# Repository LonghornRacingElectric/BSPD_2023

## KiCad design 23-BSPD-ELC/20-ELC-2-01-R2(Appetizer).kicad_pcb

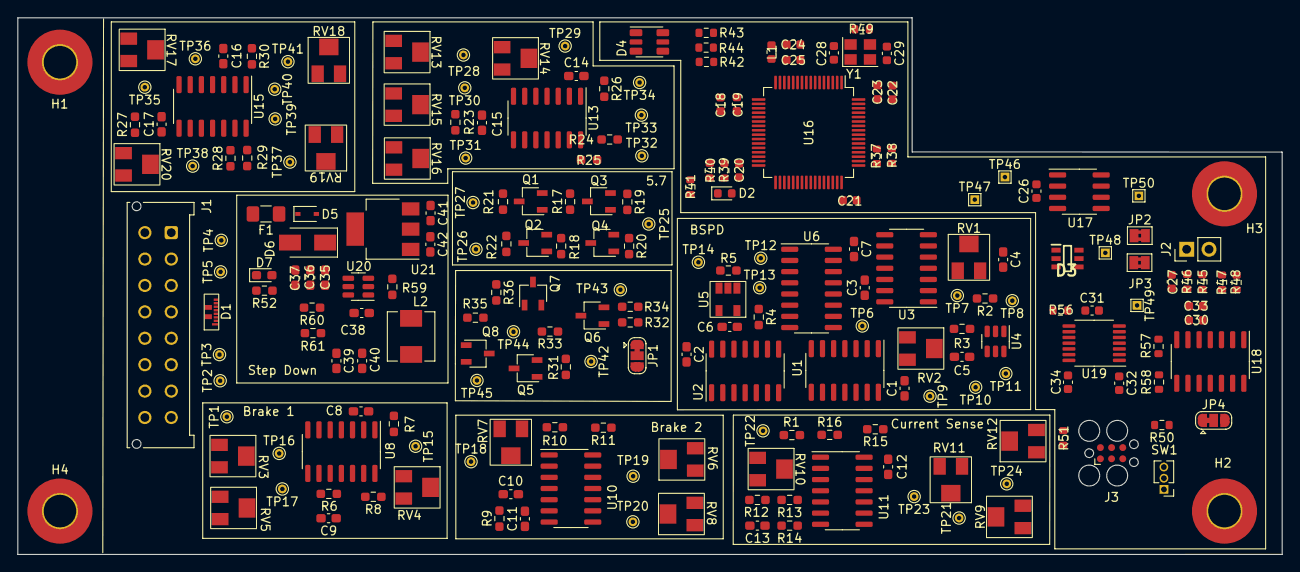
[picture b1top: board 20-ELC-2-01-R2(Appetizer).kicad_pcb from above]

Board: 2 copper layers, 143.6 x 61.0 mm, 218 parts (0 on the bottom side), 109 nets, no tracks yet.

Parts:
C1, C2, C3, C6, C7, C8, C9, C10, C11, C12, C13, C14, C15, C16, C17: 0.1uF; C_0603_1608Metric_Pad1.08x0.95mm_HandSolder
C4, C5, C39, C40, C42: 22uF; C_0603_1608Metric_Pad1.08x0.95mm_HandSolder
C18: 4u7; C_0603_1608Metric
C19, C20, C21, C22, C23: 100n; C_0603_1608Metric
C24: 1u; C_0603_1608Metric
C25: 10n; C_0603_1608Metric
C26: 0u1; C_0603_1608Metric
C27: 4.7n; C_0603_1608Metric
C28, C29: 10p; C_0603_1608Metric
C30, C32, C34: .1uF; C_0603_1608Metric
C31: 1uF; C_0603_1608Metric
C33: 10uF; C_0603_1608Metric
C35, C36: 10uF; C_0603_1608Metric_Pad1.08x0.95mm_HandSolder
C37, C38: 100nF; C_0603_1608Metric_Pad1.08x0.95mm_HandSolder
C41: 1uF; C_0603_1608Metric_Pad1.08x0.95mm_HandSolder
D1: ESD7016MUTAG
D2: RED; LED_0603_1608Metric
D3: DT1446-04TS-7; SOT95P280X100-6N
D4: SMLVN6RGB; LED_ROHM_SMLVN6
D5: 32V; D_SOD-323
D6: 0.7dV; D_SMA
D7: LED; LED_0603_1608Metric_Pad1.05x0.95mm_HandSolder
F1: 2A; Fuse_1206_3216Metric_Pad1.42x1.75mm_HandSolder
H1, H2, H3, H4: MountingHole; MountingHole_3.7mm_Pad_TopBottom
J1: Conn_02x08_Counter_Clockwise; Molex_Micro-Fit_3.0_43045-1612_2x08_P3.00mm_Vertical
J2: Conn_01x02; PinHeader_1x02_P2.54mm_Vertical
J3: SWD; Tag-Connect_TC2030-IDC-FP_2x03_P1.27mm_Vertical
JP1, JP4: Jumper_3_Bridged12; SolderJumper-3_P1.3mm_Bridged12_RoundedPad1.0x1.5mm
JP2, JP3: SolderJumper-2_P1.3mm_Bridged2Bar_Pad1.0x1.5mm
L1: 68n; L_0603_1608Metric
L2: 4u7; L_Sunlord_MWSA0518_5.4x5.2mm
Q1, Q2: Q_PMOS_GSD; TSOT-23
Q3, Q4, Q5, Q6: Q_NMOS_GSD-Device; TSOT-23
Q7, Q8: Q_PMOS_DSG; TSOT-23
R1, R2, R3, R4, R7, R8, R10, R11, R15, R16, R17, R19, R20, R21, R22, R24, R25, R26, R28, R29, R30, R33, R34, R35, R36: 10k; R_0603_1608Metric_Pad0.98x0.95mm_HandSolder
R5: 100k; R_0603_1608Metric_Pad0.98x0.95mm_HandSolder
R6, R9, R12: 510k; R_0603_1608Metric_Pad0.98x0.95mm_HandSolder
R13, R14: 150; R_0603_1608Metric_Pad0.98x0.95mm_HandSolder
R18: 250; R_0603_1608Metric_Pad0.98x0.95mm_HandSolder
R23, R27: 510; R_0603_1608Metric_Pad0.98x0.95mm_HandSolder
R31, R32: 25; R_0603_1608Metric_Pad0.98x0.95mm_HandSolder
R37, R38, R39, R40: 2k2; R_0603_1608Metric
R41: 100; R_0603_1608Metric
R42, R43, R44: 220; R_0603_1608Metric
R45, R46, R47, R48: 120; R_0603_1608Metric
R49: 47; R_0603_1608Metric
R50: 10K; R_0603_1608Metric
R51: 22; R_0603_1608Metric
R52: 470R; R_0603_1608Metric_Pad0.98x0.95mm_HandSolder
R56: 100k; R_0603_1608Metric
R57, R58: 10k; R_0603_1608Metric
R59, R60: 10K; R_0603_1608Metric_Pad0.98x0.95mm_HandSolder
R61: 54.9K; R_0603_1608Metric_Pad0.98x0.95mm_HandSolder
RV1, RV2, RV3, RV4, RV5, RV6, RV7, RV8, RV9, RV10, RV11, RV12: PVG5A104C03R00; PVG5A
RV13, RV14, RV17, RV18: 10k; PVG5A
RV15, RV16, RV19, RV20: R_POT_TRIM-Device; PVG5A
SW1: SW_SPDT; PinHeader_1x03_P1.27mm_Vertical
TP1, TP2, TP3, TP4, TP5, TP26, TP27, TP42, TP43, TP44, TP45: TestPoint-Connector; TestPoint_THTPad_D1.0mm_Drill0.5mm
TP6, TP7, TP8, TP9, TP10, TP11, TP12, TP13, TP14, TP15, TP16, TP17, TP18, TP19, TP20, TP21, TP22, TP23, TP24, TP25, TP28, TP29, TP30, TP31, TP32, TP33, TP34, TP35, TP36, TP37, TP38, TP39, TP40, TP41: TestPoint; TestPoint_THTPad_D1.0mm_Drill0.5mm
TP46, TP47, TP48, TP49, TP50: TestPoint_THTPad_1.0x1.0mm_Drill0.5mm
U1: SN74ALS32DR; SOIC-14_3.9x8.7mm_P1.27mm
U2: 74HC04D,653; SO-14_3.9x8.65mm_P1.27mm
U3: 74HC08D,653; SOIC-14_3.9x8.7mm_P1.27mm
U4: 74LVC2G17DBVE4; SOT-23-6
U5: APX823-44W5G-7; AXP823-44W5G-7
U6: CD4043BDR; SOIC-16_3.9x9.9mm_P1.27mm
U8, U10, U11, U13, U15: LM239; SO-14_3.9x8.65mm_P1.27mm
U16: STM32F105RCTx; LQFP-64_10x10mm_P0.5mm
U17: SN65HVD230; SOIC-8_3.9x4.9mm_P1.27mm
U18: MCP3428; SOIC-14_3.9x8.7mm_P1.27mm
U19: LSF0204QPWRQ1; TSSOP-14_4.4x5mm_P0.65mm
U20: LMR51420; SOT-23-6
U21: AMS1117-3.3; SOT-223-3_TabPin2
Y1: 16MHz; Crystal_SMD_3225-4Pin_3.2x2.5mm

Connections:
+3.3VA: C24.1, C25.1, L1.2, U16.13 (VDDA)
+3V3: C18.1, C19.1, C20.1, C21.1, C22.1, C23.1, C26.1, C32.1, C42.1, D2.2 (A), D4.1 (BA), D4.2 (RA), D4.3 (GA), J3.1, L1.1, R37.1, R38.1, R39.1, R40.1, R56.2, SW1.1 (A), U16.1 (VBAT), U16.19 (VDD), U16.32 (VDD), U16.48 (VDD), U16.64 (VDD), U17.3 (VCC), U19.1 (VREF_A), U21.2 (VO)
+5V: C1.1, C2.1, C3.1, C6.1, C7.1, C8.1, C10.1, C12.1, C14.1, C16.1, C30.1, C33.1, C34.1, C39.1, C40.1, C41.1, D3.5 (VCC), L2.2, R4.2, R7.2, R8.1, R10.2, R11.1, R15.2, R16.1, R24.1, R25.1, R26.1, R28.1, R29.1, R30.1, R57.2, R58.2, R61.2, RV3.1, RV4.1, RV5.1, RV6.1, RV7.1, RV8.1, RV9.1, RV10.1, RV11.1, RV12.1, RV13.1, RV14.1, RV15.1, RV16.1, RV17.1, RV18.1, RV19.1, RV20.1, U1.14 (VCC), U2.14 (VCC), U3.14 (Vcc), U4.5 (VCC), U5.5 (Vcc), U6.16 (Vdd), U8.3 (V+), U10.3 (V+), U11.3 (V+), U13.3 (V+), U15.3 (V+), U18.6 (VDD), U19.14 (VREF_B), U21.3 (VI)
+24V: F1.2, J1.1
/5.7/APPS_Trip: Q3.1 (G), Q4.1 (G), R19.2, R20.2, TP25.1, U16.40 (PC9)
/5.7/APPs1_Out: Q1.3 (D), R21.2, TP27.1
/5.7/APPs2_Out: Q2.3 (D), R22.2, TP26.1
/5.7/microcontroller/BOOT0: R50.2, U16.60 (BOOT0)
/5.7/microcontroller/CAN1_RX: TP47.1, U16.61 (PB8), U17.4 (R)
/5.7/microcontroller/CAN1_TX: TP46.1, U16.62 (PB9), U17.1 (D)
/5.7/microcontroller/HSE_in: C28.1, U16.5 (PD0), Y1.1
/5.7/microcontroller/HSE_out: R49.1, U16.6 (PD1)
/5.7/microcontroller/I2C1_SCL: R37.2, U16.58 (PB6)
/5.7/microcontroller/I2C1_SDA: R38.2, U16.59 (PB7)
/5.7/microcontroller/I2C2_SCL: R39.2, U16.29 (PB10)
/5.7/microcontroller/I2C2_SDA: R40.2, U16.30 (PB11)
/5.7/microcontroller/LED_B: R42.2, U16.16 (PA2)
/5.7/microcontroller/LED_G: R43.2, U16.15 (PA1)
/5.7/microcontroller/LED_R: R44.2, U16.14 (PA0)
/5.7/microcontroller/SWCLK: J3.4, U16.49 (PA14)
/5.7/microcontroller/SWDIO: R51.2, U16.46 (PA13)
/24 to 5V Step Down/BUCK/EN: R59.2, U20.5 (EN)
/24 to 5V Step Down/BUCK/SW: C38.1, L2.1, U20.2 (SW)
/24 to 5V Step Down/BUCK/VBST: C38.2, U20.6 (VBST)
/24 to 5V Step Down/BUCK/VFB: R60.1, R61.1, U20.4 (VFB)
/24 to 5V Step Down/BUCK/V_in: C35.1, C36.1, C37.1, D6.1 (K), D7.2 (A), R59.1, U20.3 (VIN)
/24 to 5V Step Down/DIODE: D5.1 (K), D6.2 (A), F1.1
/APPs1_5%: R25.2, TP32.1, U13.14, U16.39 (PC8)
/APPs1_25%: R24.2, TP33.1, U13.13, U16.10 (PC2)
/APPs1_Connected: R26.2, TP34.1, U13.1, U13.2, U16.38 (PC7)
/APPs1_Signal_Raw: C15.1, D1.7 (I/O5), J1.2, Q1.2 (S), R17.2, R23.1, TP4.1, U13.5 (+), U13.6 (-), U13.8 (-), U13.11 (+)
/APPs2_5%: R29.2, TP39.1, U15.14, U16.8 (PC0)
/APPs2_25%: R28.2, TP40.1, U15.13, U16.11 (PC3)
/APPs2_Connected: R30.2, TP41.1, U15.1, U15.2, U16.37 (PC6)
/APPs2_Signal_Raw: C17.1, D1.8 (I/O6), J1.3, Q2.2 (S), R18.2, R27.1, TP5.1, U15.5 (+), U15.6 (-), U15.8 (-), U15.11 (+)
/BMS Signal/DataRaw_Half: R13.1, R14.1, U11.5 (+), U11.6 (-), U11.9 (+), U11.10 (-)
/BSPD_Reset: J1.7, U5.3 (~MR)
/Brake1 Signal/Vref_4V: RV3.2, TP16.1, U8.7 (+), U8.11 (+)
/Brake1_Connected: R8.2, U2.1, U8.13, U8.14
/Brake1_Signal: J1.15, R7.1, U1.1, U8.1, U8.2, U16.25 (PC5)
/Brake1_Signal_Raw: C9.1, D1.4 (I/O3), J1.4, R6.2, TP2.1, U8.5 (+), U8.6 (-), U8.9 (+), U8.10 (-)
/Brake2 Signal/Vref_4V: RV6.2, TP19.1, U10.7 (+), U10.11 (+)
/Brake2_Connected: R11.2, U2.3, U10.13, U10.14
/Brake2_Signal: R10.1, U1.2, U2.9, U10.1, U10.2, U16.24 (PC4)
/Brake2_Signal_Raw: C11.1, D1.2 (I/O2), J1.5, R9.2, TP1.1, U10.5 (+), U10.6 (-), U10.9 (+), U10.10 (-)
/BrakeSystemPlausibilityDevice/Power_and_Brakes: RV1.1, TP7.1, U3.3 (1Y)
/BrakeSystemPlausibilityDevice/Power_and_Brakes_TRIP: TP11.1, U1.4, U4.6
/BrakeSystemPlausibilityDevice/SET: R5.1, TP13.1, U5.1 (~Reset), U6.4 (S1)
/BrakeSystemPlausibilityDevice/Signal_Lost: RV2.1, U1.11
/BrakeSystemPlausibilityDevice/Signal_Lost_TRIP: TP10.1, U1.5, U4.4
/BrakeSystemPlausibilityDevice/TRIP: TP12.1, U1.6, U6.3 (R1)
/BrakeSystemPlausibilityDevice/~Brake1_Connected: U1.9, U2.2
/BrakeSystemPlausibilityDevice/~Brake2_Connected: U1.10, U2.4
/BrakeSystemPlausibilityDevice/~Brake_Connected: U1.8, U1.12
/BrakeSystemPlausibilityDevice/~CS_Connected: U1.13, U2.6
/CurrentSense_Connected: R15.1, U2.5, U11.13, U11.14
/CurrentSense_Signal: R1.1, R16.2, U3.1 (1A), U11.1, U11.2
/Current_Sense_Signal_Raw: C13.1, D1.1 (I/O1), J1.6, R12.2, R13.2, TP3.1
/Shutdown_IN: J1.11, Q7.3 (D), R36.1
/Shutdown_OUT: J1.10, Q8.2 (S), TP45.1
/VCU_Control: J1.9, JP1.3 (B)
/Watchdog/SCL: R58.1, U18.8 (SCL)
/Watchdog/SDA: R57.1, U18.7 (SDA)
/~BSPD_TRIPPED: JP1.1 (A), R32.1, TP14.1, U6.2 (Q1)
/~Brake2_Signal: J1.14, U2.8
GND: C1.2, C2.2, C3.2, C4.2, C5.2, C6.2, C7.2, C8.2, C9.2, C10.2, C11.2, C12.2, C13.2, C14.2, C15.2, C16.2, C17.2, C18.2, C19.2, C20.2, C21.2, C22.2, C23.2, C24.2, C25.2, C26.2, C27.1, C28.2, C29.2, C30.2, C31.2, C32.2, C33.2, C34.2, C35.2, C36.2, C37.2, C39.2, C40.2, C41.2, C42.2, D1.3 (VBUS_OR_GND), D3.2 (VSS), D5.2 (A), J1.8, J3.5, Q3.2 (S), Q4.2 (S), Q6.2 (S), R1.2, R2.2, R3.2, R5.2, R6.1, R9.1, R12.1, R14.2, R19.1, R20.1, R21.1, R22.1, R23.2, R27.2, R34.2, R41.2, R52.1, R60.2, RV3.3, RV4.3, RV5.3, RV6.3, RV7.3, RV8.3, RV9.3, RV10.3, RV11.3, RV12.3, RV13.3, RV14.3, RV15.3, RV16.3, RV17.3, RV18.3, RV19.3, RV20.3, SW1.3 (C), U1.7 (GND), U2.7 (GND), U2.11, U2.13, U3.4 (2A), U3.5 (2B), U3.7 (GND), U3.9 (3A), U3.10 (3B), U3.12 (4A), U3.13 (4B), U4.2 (GND), U5.2 (GND), U6.6 (S2), U6.7 (R2), U6.8 (Vss), U6.11 (R3), U6.12 (S3), U6.14 (S4), U6.15 (R4), U8.12 (V-), U10.12 (V-), U11.12 (V-), U13.12 (V-), U15.12 (V-), U16.12 (VSSA), U16.18 (VSS), U16.31 (VSS), U16.47 (VSS), U16.63 (VSS), U17.2 (GND), U17.8 (Rs), U18.2 (CH1-), U18.4 (CH2-), U18.5 (VSS), U18.9 (Adr0), U18.10 (Adr1), U18.12 (CH3-), U18.14 (CH4-), U19.7 (GND), U20.1 (GND), U21.1 (GND), Y1.2, Y1.4
unnamed: C4.1, R2.1, RV1.2, TP8.1, U4.1
unnamed: C5.1, R3.1, RV2.2, TP9.1, U4.3
unnamed: C27.2, J2.1, R45.1, R46.1
unnamed: C29.1, R49.2, Y1.3
unnamed: C31.1, R56.1, U19.8 (EN)
unnamed: D2.1 (K), R41.1
unnamed: D3.4 (I/O3), JP3.1 (A), R45.2, R46.2, TP49.1, U17.6 (CANL)
unnamed: D3.6 (I/O4), JP2.1 (A), R47.1, R48.1, TP48.1, TP50.1, U17.7 (CANH)
unnamed: D4.4 (GK), R44.1
unnamed: D4.5 (RK), R43.1
unnamed: D4.6 (BK), R42.1
unnamed: D7.1 (K), R52.2
unnamed: J2.2, R47.2, R48.2
unnamed: J3.2, R51.1
unnamed: JP1.2 (C), R31.1
unnamed: JP4.2 (C), U19.3 (A2)
unnamed: Q1.1 (G), Q3.3 (D), R17.1
unnamed: Q2.1 (G), Q4.3 (D), R18.1
unnamed: Q5.1 (G), R31.2, R33.1, TP42.1
unnamed: Q5.2 (S), R33.2
unnamed: Q5.3 (D), Q8.1 (G), R35.2
unnamed: Q6.1 (G), R32.2, R34.1, TP43.1
unnamed: Q6.3 (D), Q7.1 (G), R36.2
unnamed: Q7.2 (S), Q8.3 (D), R35.1, TP44.1
unnamed: R4.1, U6.5 (Enable)
unnamed: R50.1, SW1.2 (B)
unnamed: RV4.2, TP15.1, U8.4 (-)
unnamed: RV5.2, TP17.1, U8.8 (-)
unnamed: RV7.2, TP18.1, U10.4 (-)
unnamed: RV8.2, TP20.1, U10.8 (-)
unnamed: RV9.2, TP21.1, U11.7 (+)
unnamed: RV10.2, TP22.1, U11.4 (-)
unnamed: RV11.2, TP23.1, U11.8 (-)
unnamed: RV12.2, TP24.1, U11.11 (+)
unnamed: RV13.2, TP28.1, U13.7 (+)
unnamed: RV14.2, TP29.1, U13.4 (-)
unnamed: RV15.2, TP30.1, U13.10 (-)
unnamed: RV16.2, TP31.1, U13.9 (+)
unnamed: RV17.2, TP35.1, U15.7 (+)
unnamed: RV18.2, TP36.1, U15.4 (-)
unnamed: RV19.2, TP37.1, U15.10 (-)
unnamed: RV20.2, TP38.1, U15.9 (+)
unnamed: TP6.1, U1.3, U3.2 (1B)

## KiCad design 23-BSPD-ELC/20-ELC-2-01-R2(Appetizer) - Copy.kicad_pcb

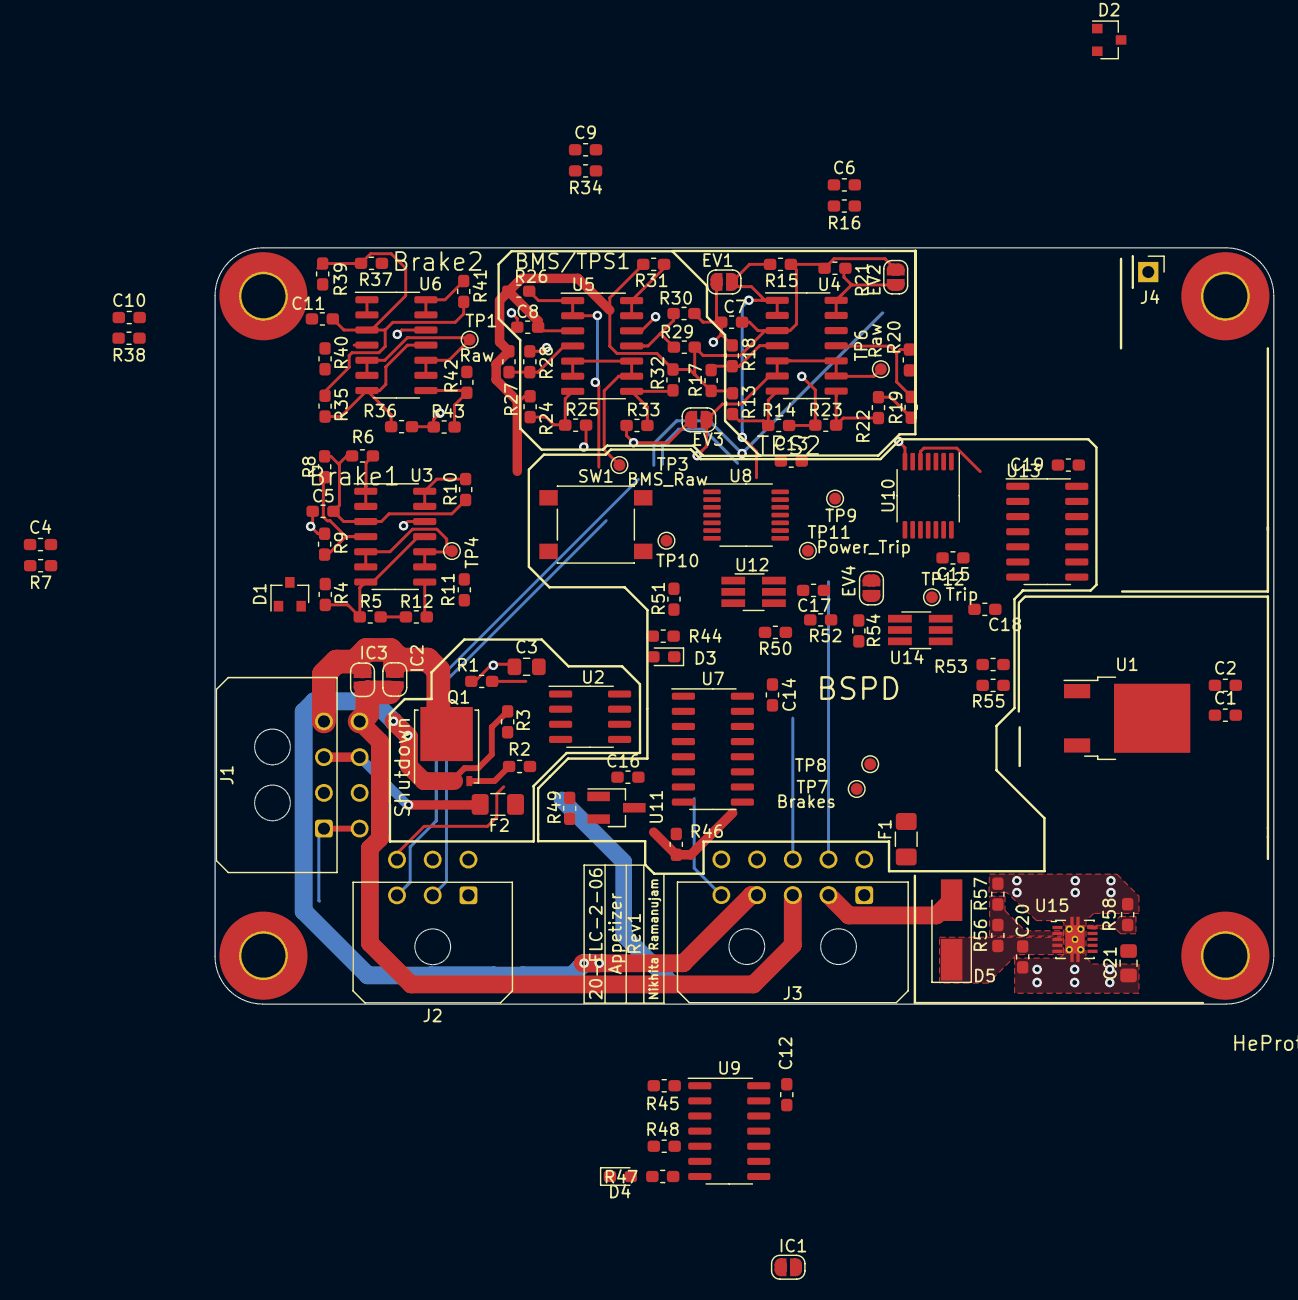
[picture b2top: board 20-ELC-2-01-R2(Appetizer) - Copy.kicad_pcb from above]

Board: 2 copper layers, 88.9 x 63.5 mm, 128 parts (0 on the bottom side), 65 nets.

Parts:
C1: 0.33uF; C_0603_1608Metric_Pad1.05x0.95mm_HandSolder
C2, C4, C5, C6, C7, C8, C9, C10, C11, C12, C13, C14, C15, C16, C17, C18, C19, C20: 0.1uF; C_0603_1608Metric_Pad1.05x0.95mm_HandSolder
C3, C21: 1uF; C_0805_2012Metric_Pad1.15x1.40mm_HandSolder
D1, D2: PSM712-LF-T7; SOT-23
D3, D4: LED; LED_0603_1608Metric_Pad1.05x0.95mm_HandSolder
D5: SS54; D_SMA_Handsoldering
EV1, EV2, EV3, EV4: Jumper_NO; SolderJumper-2_P1.3mm_Open_RoundedPad1.0x1.5mm
F1, F2: 1A; Fuse_1206_3216Metric_Pad1.42x1.75mm_HandSolder
H1, H2, H3, H4: MountingHole; MountingHole_3.7mm_Pad_TopBottom
IC1, IC2, IC3: Jumper_NO; SolderJumper-2_P1.3mm_Open_RoundedPad1.0x1.5mm
J1: Conn_02x04_Top_Bottom; Molex_Micro-Fit_3.0_43045-0800_2x04_P3.00mm_Horizontal
J2: Conn_02x03_Top_Bottom; Molex_Micro-Fit_3.0_43045-0600_2x03_P3.00mm_Horizontal
J3: Conn_02x05_Top_Bottom; Molex_Micro-Fit_3.0_43045-1000_2x05_P3.00mm_Horizontal
J4: Conn_01x01; PinHeader_1x01_P2.54mm_Vertical
Q1: CSD18512Q5B; TDSON-8-1
R1, R3, R50, R53: 1M; R_0603_1608Metric_Pad1.05x0.95mm_HandSolder
R2: 220; R_0603_1608Metric_Pad1.05x0.95mm_HandSolder
R4, R6, R10, R12, R13, R15, R21, R24, R26, R29, R31, R33, R35, R37, R41, R43, R45, R46, R48, R49: 10k; R_0603_1608Metric_Pad1.05x0.95mm_HandSolder
R5, R11, R14, R20, R22, R25, R30, R32, R36, R42: 40.2k; R_0603_1608Metric_Pad1.05x0.95mm_HandSolder
R7, R16, R34, R38: 510k; R_0603_1608Metric_Pad1.05x0.95mm_HandSolder
R8, R27, R39: 20k; R_0603_1608Metric_Pad1.05x0.95mm_HandSolder
R9, R28, R40: 30.1k; R_0603_1608Metric_Pad1.05x0.95mm_HandSolder
R17, R18: 0; R_0603_1608Metric_Pad1.05x0.95mm_HandSolder
R19, R23: 5k; R_0603_1608Metric_Pad1.05x0.95mm_HandSolder
R44, R47: 4.7k; R_0603_1608Metric_Pad1.05x0.95mm_HandSolder
R51: 180k; R_0603_1608Metric_Pad1.05x0.95mm_HandSolder
R52: 680k; R_0603_1608Metric_Pad1.05x0.95mm_HandSolder
R54: 150k; R_0603_1608Metric_Pad1.05x0.95mm_HandSolder
R55: 523k; R_0603_1608Metric_Pad1.05x0.95mm_HandSolder
R56: 100k; R_0603_1608Metric_Pad1.05x0.95mm_HandSolder
R57: 25k; R_0603_1608Metric_Pad1.05x0.95mm_HandSolder
R58: 43k; R_0603_1608Metric_Pad1.05x0.95mm_HandSolder
SW1: UK-B0228-G5-160-JZ; SW_Push_1P1T_NO_6x6mm_H9.5mm
TP1, TP3, TP4, TP6, TP7, TP8, TP9, TP10, TP11, TP12: TestPoint; TestPoint_Pad_D1.0mm
U1: L78M05ABDT-TR; TO-252-2
U2: MIC5014YM; SOIC-8_3.9x4.9mm_P1.27mm
U3, U4, U5, U6: LM239; SO-14_3.9x8.65mm_P1.27mm
U7: HEF4043B; SOIC-16_3.9x9.9mm_P1.27mm
U8, U10: SN74HC32PWR; TSSOP-14_4.4x5mm_P0.65mm
U9: 74HC08D,653; SOIC-14_3.9x8.7mm_P1.27mm
U11: TLV810; SOT-23_Handsoldering
U12, U14: LTC6994-1; TSOT-23-6_HandSoldering
U13: 74HC04; SO-14_3.9x8.65mm_P1.27mm
U15: TPS259261DRCR; VSON-10-1EP_3x3mm_P0.5mm_EP1.65x2.4mm_ThermalVias

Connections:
+5V: C2.1, C5.1, C7.1, C8.1, C11.1, C12.1, C13.1, C14.1, C15.2, C16.1, C17.1, C18.1, C19.1, D3.2, EV2.1, F1.2, F2.2, IC1.2, R4.2, R6.2, R8.2, R10.2, R11.2, R13.2, R15.2, R17.2, R19.2, R21.2, R22.2, R24.2, R26.2, R27.2, R29.2, R31.2, R32.2, R35.2, R37.2, R39.2, R41.2, R42.2, R46.2, R50.1, R53.1, SW1.1, U1.3, U3.3, U4.3, U5.3, U6.3, U7.16, U8.14, U9.14, U10.14, U11.3, U12.5, U13.14, U14.5
+12V: C1.2, C3.2, C21.1, U1.1, U2.1, U15.6, U15.7, U15.8
/12V_Raw: D5.2, J3.2
/BMS_or_TPS1_Connected: R31.1, U5.13, U5.14, U13.5
/BMS_or_TPS1_Signal: R26.1, U5.1, U5.2, U8.4
/BMS_or_TPS1_Signal_Raw: C9.1, D2.1, J3.7, R34.2, TP3.1, U5.5, U5.6, U5.9, U5.10
/BOTS-: IC2.2, IC3.2, J1.4, Q1.5
/Brake1 Signal/Vref_4V: R4.1, R5.2, U3.7, U3.11
/Brake1_Connected: R10.1, U3.13, U3.14, U13.1
/Brake1_Signal: J2.2, R6.1, U3.1, U3.2, U8.1, U13.11
/Brake1_Signal_Raw: C4.1, D1.2, J1.2, R7.2, TP4.1, U3.5, U3.6, U3.9, U3.10
/Brake2 Signal/Vref_4V: R35.1, R36.2, U6.7, U6.11
/Brake2_Connected: R41.1, U6.13, U6.14, U13.3
/Brake2_Signal: J2.3, R37.1, U6.1, U6.2, U8.2
/Brake2_Signal_Raw: C10.1, D1.1, J1.6, R38.2, TP1.1, U6.5, U6.6, U6.9, U6.10
/BrakeSystemPlausibilityDevice/BMS_or_Throttle: R45.1, U8.6, U9.1
/BrakeSystemPlausibilityDevice/Brakes_and_Power_TRIP: TP11.1, U8.9, U12.6
/BrakeSystemPlausibilityDevice/Power_and_Brakes: TP7.1, U9.3, U12.1
/BrakeSystemPlausibilityDevice/SET: R49.1, SW1.2, TP10.1, U7.4, U11.2
/BrakeSystemPlausibilityDevice/Signal_Lost: EV4.1, U10.8, U14.1
/BrakeSystemPlausibilityDevice/Signal_Lost_TRIP: EV4.2, TP12.1, U8.10, U14.6
/BrakeSystemPlausibilityDevice/TRIP: TP9.1, U7.3, U8.8
/BrakeSystemPlausibilityDevice/~BMS_or_TPS1_Connected: U10.4, U13.6
/BrakeSystemPlausibilityDevice/~BMS_or_TPS_Connected: U10.6, U10.10
/BrakeSystemPlausibilityDevice/~Brake1_Connected: U10.1, U13.2
/BrakeSystemPlausibilityDevice/~Brake2_Connected: U10.2, U13.4
/BrakeSystemPlausibilityDevice/~Brake_Connected: U10.3, U10.9
/BrakeSystemPlausibilityDevice/~TPS2_Connected: U10.5, U13.8
/Connectors/BOTS+: IC2.1, IC3.1, J1.8, J3.3
/Shutdown_Control: R1.2, R47.2, U2.2, U9.6
/Shutdown_Out: J3.4, Q1.1, Q1.2, Q1.3, R3.1, U2.3
/TPS2_Connected: EV2.2, R21.1, U4.13, U4.14, U13.9
/TPS2_Signal: EV1.1, R15.1, U4.1, U4.2, U8.5
/TPS2_Signal_Raw: C6.1, D2.2, EV3.1, J3.8, R16.2, TP6.1, U4.5, U4.6, U4.9, U4.10
/VCU_Relay_Control: IC1.1, J2.4, R48.1, U9.5
/~BSPD_TRIPPED: J2.6, J3.5, R44.1, U7.2, U9.4
/~Brake1_Signal: J2.5, U13.10
GND: C1.1, C2.2, C3.1, C4.2, C5.2, C6.2, C7.2, C8.2, C9.2, C10.2, C11.2, C12.2, C13.2, C14.2, C15.1, C16.2, C17.2, C18.2, C19.2, C20.2, C21.2, D1.3, D2.3, D4.1, EV1.2, EV3.2, J1.1, J1.5, J2.1, J3.1, J3.9, J4.1, R1.1, R5.1, R7.1, R9.1, R12.1, R14.1, R16.1, R18.1, R20.1, R23.1, R25.1, R28.1, R30.1, R33.1, R34.1, R36.1, R38.1, R40.1, R43.1, R45.2, R48.2, R49.2, R51.2, R52.2, R54.2, R55.2, R57.2, R58.2, U1.2, U2.4, U3.12, U4.12, U5.12, U6.12, U7.6, U7.7, U7.8, U7.11, U7.12, U7.14, U7.15, U8.7, U8.12, U8.13, U9.7, U9.9, U9.10, U9.12, U9.13, U10.7, U10.12, U10.13, U11.1, U12.2, U13.7, U13.13, U14.2, U15.11
unnamed: C20.1, D5.1, R56.1, U15.3, U15.4, U15.5
unnamed: D3.1, R44.2
unnamed: D4.2, R47.1
unnamed: F1.1, J3.6
unnamed: F2.1, J1.3, J1.7
unnamed: Q1.4, R2.1, R3.2
unnamed: R2.2, U2.5
unnamed: R8.1, R9.2, U3.4
unnamed: R11.1, R12.2, U3.8
unnamed: R13.1, R14.2, U4.7
unnamed: R17.1, R18.2, U4.4
unnamed: R19.1, R20.2, U4.11
unnamed: R22.1, R23.2, U4.8
unnamed: R24.1, R25.2, U5.7
unnamed: R27.1, R28.2, U5.4
unnamed: R29.1, R30.2, U5.11
unnamed: R32.1, R33.2, U5.8
unnamed: R39.1, R40.2, U6.4
unnamed: R42.1, R43.2, U6.8
unnamed: R46.1, U7.5
unnamed: R50.2, R52.1, U12.4
unnamed: R51.1, U12.3
unnamed: R53.2, R55.1, U14.4
unnamed: R54.1, U14.3
unnamed: R56.2, R57.1, U15.2
unnamed: R58.1, U15.10
unnamed: TP8.1, U8.3, U9.2

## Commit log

2022-09-26 Added 2023KicadLibrary
2022-11-26 23-BSPD updated schematic. Please ignore the backup files.
2022-12-04 Updated connectors and added ~brake signal to vcu
2022-12-12 Revision changes and updates to some footprints
2023-01-07 Updated pcb layout; Watchdog on board still in progress
2023-01-10 BSPD layout
